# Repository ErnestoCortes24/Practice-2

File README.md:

# Practice 2. Developiong the PCB (Layout)

## Objectives

Develop the connection diagrams (layout) from the schematic diagram.

## Introduction

Microcontrollers are all around  he world. Each day, Microcontrollers, are more present in the many aspects of our lives: in our work, inside our houses, and in more. We can find them controlling small devices like cellphones, microwaves, washing machines, and televisions.

A microcontroller is one device or chip that is used to govern one or more processes. For example, the controller that regulates the room temperature of an air conditioner; it has a sensor that continuously measures the internal temperature and, when the preset limits are exceeded, it generates the necessary signals to adjust the temperature.

## State of the Art

### The practices and the PIC microcontroller

The main objective of this practices is to provide students the foundation to fully understand the operation of the PIC18F45K50 microcontroller. This will be achieved through 11 documents that will guide the reader to create their own electronic card or Printed Circuit Board (PCB) and to be able to program it; in order to, execute different functions.

The advantages of ta PIC microcontroller to others on the market, which is why it will be used throughout this manual, are as follows:

- Easy to operate.
- There is enough documentation to work with it and it’s easy to obtain it.
- The price is comparatively lower than its competitors.
- It has a high operating speed.
- Development tools are cheap and easy to use.
- There are a variety of hardware that can record, erase and check the behavior of PIC.
- Once you learn to handle a PIC, it will easier to handle any other models of microcontrollers.

### KiCad EDA Software

KiCad is an open source software suite for Electronic Design Automation (EDA). The programs handle Schematic Capture,
and PCB Layout with Gerber output. The suite runs on Windows, Linux and macOS and is licensed under GNU GPL v3. The
first release date was in 1992 by its original author, Jean-Pierre Charras, but is now currently under development by
the KiCad Developers Team. 

## Results

In this section, you must report the outcomes of the laboratory activities.

### Follow the next 'Project Configuration' Steps

1. In  the  same  project  from  practice  1,  click  on  the  icon ‘Assign PCB footprints to schematic symbols’.  By  doing  so,  you  will  be  able  to  watch  the  footprints associations in a list format. ***NOTE:*** *If a ***‘Confirmation’*** window pops to reassign all the components to a new library format, click ‘No.’*

2. Now it is time to add the corresponding libraries to the Cvpcbprogram.   Download from [here](./modules)  the modules   needed   for   the   project.   Click   on Preferences→Manage Footprint Libraries...and  in this  way  you  will  be  able  to  add  the  modules  from the folder  named  ‘modules.’  Click  on  ‘Project  Specific Libraries...’  tab,  then  click  on  the  button  ‘Browse Libraries...’ and search for the folder  where  you  save the modules. Select all the files and click ‘OK.’Fig.  1 shows the result of the added modules. NOTE:Your KiCad EDA Software must be in english to add the modules.

3. Once  that  is  done,  you  must  associate  the  list  of components  with  its  respective  footprint using Table  I for  guidance.  Be  sure  to  activate  the  option  ‘Filter footprints  list  by  library’ from  the Cvpcbtoolbar. To associate  the  components  showed  in  the middle  column,  double  click  with  their  corresponding footprint from the right column. ***NOTE:*** *Search  all  the  footprints  in  the*  ***‘user’*** *and * 
***‘discrete’*** * added libraries that should be found at the end of the list.*

4. Save   your modifications  by  clicking  **‘Apply,  Save Schematic & Continue,’ and then click ‘OK.’**
5. After that, you may close the Cvpcband go back to the EESchema (Schematic  Editor.)  Save  your  project  by clicking   on File→Save.   Close   the   editor   of   the Schematic and switch back to the **‘Project Manager.’**

6. Once you have the design of the circuit on the schematic, it is time to generate the **‘layout’** of our PCB  using the Netlist  file. On  the Project  Manager program  from KiCad, click on the icon **‘PCB layout editor’** . A new window will appear from the PCBNew. Click **‘Yes’** in the confirmation window.
7. On  the  toolbar  menu  from  the PCBNew click  on  the **‘Page  Settings  for  paper  size  and  texts’**
and modify the size settings to **‘USLetter 8.5x11in.’**

8. After  that,  it  will be  time  to  focus  more  on  design concepts.  You  may  do  so  by  opening  the
menu  of **‘Setup→Design Rules...’**. On   it,   some   final   design characteristics will appear with many millimeter values. Between   them,   you   should   find  the  **‘Clearance’** specification  which  is  the  smallest  spaces  that  it  must exist  between  the tracks  on the  PCB.  You  shall  set the value of this cell to 0.508 mm (0.020 inches.) Next, we set  a  value  of 1.200  mm  (0.047244 inches)on the  cell of **‘Track Width.’** 

9. Switch now to the ‘Global Design Rules’ tab and write, if needed, the minimum values for each an every one of the parameters on the ‘Minimum Allowed Values’ box. Click ‘OK.’

10. Time  to  import  the  Netlist  file.  Go  to  the  toolbar ‘Tools→Update  PCB  from  Schematic...’  and  then click on ‘Update  PCB.’ When  you  close  the  window all the components will appear on the screen.

11.Check in the ‘Layers Manager’ window (located at the right  part  of  your  screen) that all  the needed  boxes  are
checked, as shown:

11.Check in the ‘Layers Manager’ window (located at the right  part  of  your  screen) that all  the needed  boxes  are checke

12. Now you  have  to  define  the  limits  of  the  PCB.  First, highlight  the  ‘Edge.Cuts’  layer.  Then,  select  the  ‘Add  graphic lines’ tool and began to trace the original measures of your copper board (15x20 cm.) You must also define the  cutting  area;  do  not  forget  to  add  a  2.5  cm  margin around the board. To measure the lines, you can use the ‘Add dimension’ tool located on the right.

13. It is your turn to move all the components in the circuit in  order  to  avoid  any  track  intersection  inside  the working   area.   You   can   move   the   components   by positioning your mouse pointer above it and pressing the key [G]. All the components are connected to each other by a group of wires called ratsnest. Make sure that the icon  of  **‘Hide  board  ratsnest’** located  in  the toolbar of the left is highlighted.

14. Now you must link all the connections of you PCB. But before  that,  you  must  change  the  drawing  option  from the right toolbar from ‘Edge.Cuts’ to ‘B.Cu (PgDn)’ (B->Bottom, Cu->Copper.).

15. Start to connect your tracks to each and every one pin on the schematic by using the icon ‘Route Tracks’. Trace  all  the  routes  for  each  net  or  connection  in  your PCB design.

16. Once  your  are  done,  save  your  layout  File->Save  or using the command [Ctrl + S].

17. Your board must look like:

### Report
For this practice, modify only the Conclusion section. Commit an push the changes on the fork of this repository and add
upload the link on Canvas.

### File uploads
Commit and push the files with extensions .pro and .kicad_pcb created once you completed all the steps of the document in the repository.

### Demonstration
Screenshot the image of the complete schematic and upload it at the repository.

## Conclusion

In this practica, I am be able to do schematic circuits in PBC in KiCad. The instructions was not very clear at the beginning, but the rest of the practice was clear and comprehensive. I had problems adding the libreries because the explorer could no found the modules. On the other hand, I spent much time (around 2 hours) arranging the components, and I had an error in the PCB, thus, at the moment when I was connecitng each component in their place, it was missing a a wire in a resistence. In general, I can say I got the knowledge to make physical PCB's. The thing that I need to improve is spread the components to have space and have a better design.

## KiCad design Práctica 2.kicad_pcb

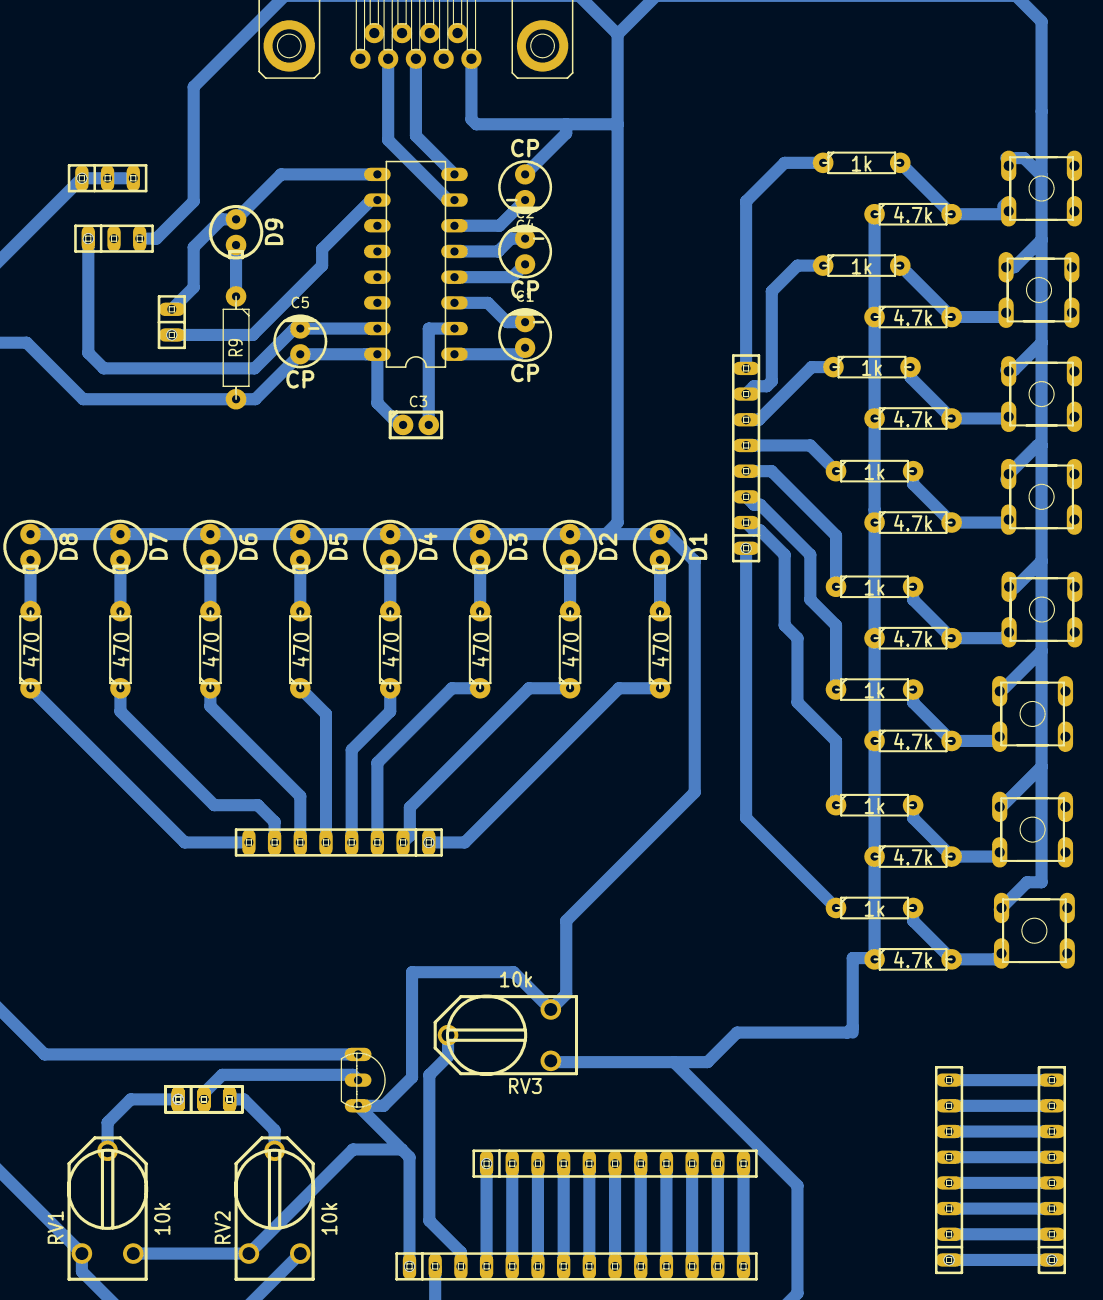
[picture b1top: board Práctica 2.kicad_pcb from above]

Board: 2 copper layers, 64 parts (0 on the bottom side), 68 nets.

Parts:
C1, C2, C4, C5: CP; Capacitor_elect
C3: CP; Capacitor
D1, D2, D3, D4, D5, D6, D7, D8, D9: LED; Led
JP1, JP2, JP3, JP3#2: PINHD-1X3; pinhead-1X03
JP4, JP8, JP9, JP10: PINHD-1X8M; pinhead-1X08
JP5: PINHD-1X14M; pinhead-1X14
JP6: PINHD-1X11M; pinhead-1X11
JP7: PINHD-1X2; pinhead-1X02
R1, R2, R3, R4, R5, R6, R7, R8: 470; Resistor
R9: 470; Resistor_large
R10, R11, R12, R13, R14, R15, R16, R17: 1k; Resistor
R18, R19, R20, R21, R22, R23, R24, R25: 4.7k; Resistor
RV1, RV2, RV3: 10k; RV2X4
S1, S2, S3, S4, S5, S6, S7, S8: DTS-6
U1: MCP9700A
U2: MAX232; Maxim232
X1: F09HP; Conector_F09HP

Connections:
+5VA: C3.1, C5.1, JP2.1, JP2.2, JP2.3, JP5.2, R9.2, R18.1, R19.1, R20.1, R21.1, R22.1, R23.1, R24.1, R25.1, RV1.1, RV2.3, RV3.1, U1.1, U2.16
GNDA: C4.1, C5.2, D1.1, D2.1, D3.1, D4.1, D5.1, D6.1, D7.1, D8.1, JP1.1, JP1.2, JP1.3, JP5.1, RV1.3, RV2.1, RV3.3, S1.1, S2.1, S3.1, S4.1, S5.1, S6.1, S7.1, S8.1, U1.3, U2.15, X1.5
unnamed: C1.1, U2.1
unnamed: C1.2, U2.3
unnamed: C2.1, U2.4
unnamed: C2.2, U2.5
unnamed: C3.2, U2.2
unnamed: C4.2, U2.6
unnamed: D1.2, R1.2
unnamed: D2.2, R2.2
unnamed: D3.2, R3.2
unnamed: D4.2, R4.2
unnamed: D5.2, R5.2
unnamed: D6.2, R6.2
unnamed: D7.2, R7.2
unnamed: D8.2, R8.2
unnamed: D9.1, JP7.2, U2.9
unnamed: D9.2, R9.1
unnamed: JP3.1, JP3#2.1, RV1.2
unnamed: JP3.2, JP3#2.2, U1.2
unnamed: JP3.3, JP3#2.3, RV2.2
unnamed: JP4.1, R1.1
unnamed: JP4.2, R2.1
unnamed: JP4.3, R3.1
unnamed: JP4.4, R4.1
unnamed: JP4.5, R5.1
unnamed: JP4.6, R6.1
unnamed: JP4.7, R7.1
unnamed: JP4.8, R8.1
unnamed: JP5.3, RV3.2
unnamed: JP5.4, JP6.1
unnamed: JP5.5, JP6.2
unnamed: JP5.6, JP6.3
unnamed: JP5.7, JP6.4
unnamed: JP5.8, JP6.5
unnamed: JP5.9, JP6.6
unnamed: JP5.10, JP6.7
unnamed: JP5.11, JP6.8
unnamed: JP5.12, JP6.9
unnamed: JP5.13, JP6.10
unnamed: JP5.14, JP6.11
unnamed: JP7.1, U2.10
unnamed: JP8.1, R10.1
unnamed: JP8.2, R11.1
unnamed: JP8.3, R12.1
unnamed: JP8.4, R13.1
unnamed: JP8.5, R14.1
unnamed: JP8.6, R15.1
unnamed: JP8.7, R16.1
unnamed: JP8.8, R17.1
unnamed: JP9.1, JP10.1
unnamed: JP9.2, JP10.2
unnamed: JP9.3, JP10.3
unnamed: JP9.4, JP10.4
unnamed: JP9.5, JP10.5
unnamed: JP9.6, JP10.6
unnamed: JP9.7, JP10.7
unnamed: JP9.8, JP10.8
unnamed: R10.2, R18.2, S1.3
unnamed: R11.2, R19.2, S2.3
unnamed: R12.2, R20.2, S3.3
unnamed: R13.2, R21.2, S4.3
unnamed: R14.2, R22.2, S5.3
unnamed: R15.2, R23.2, S6.3
unnamed: R16.2, R24.2, S7.3
unnamed: R17.2, R25.2, S8.3
unnamed: U2.7, X1.2
unnamed: U2.8, X1.3
